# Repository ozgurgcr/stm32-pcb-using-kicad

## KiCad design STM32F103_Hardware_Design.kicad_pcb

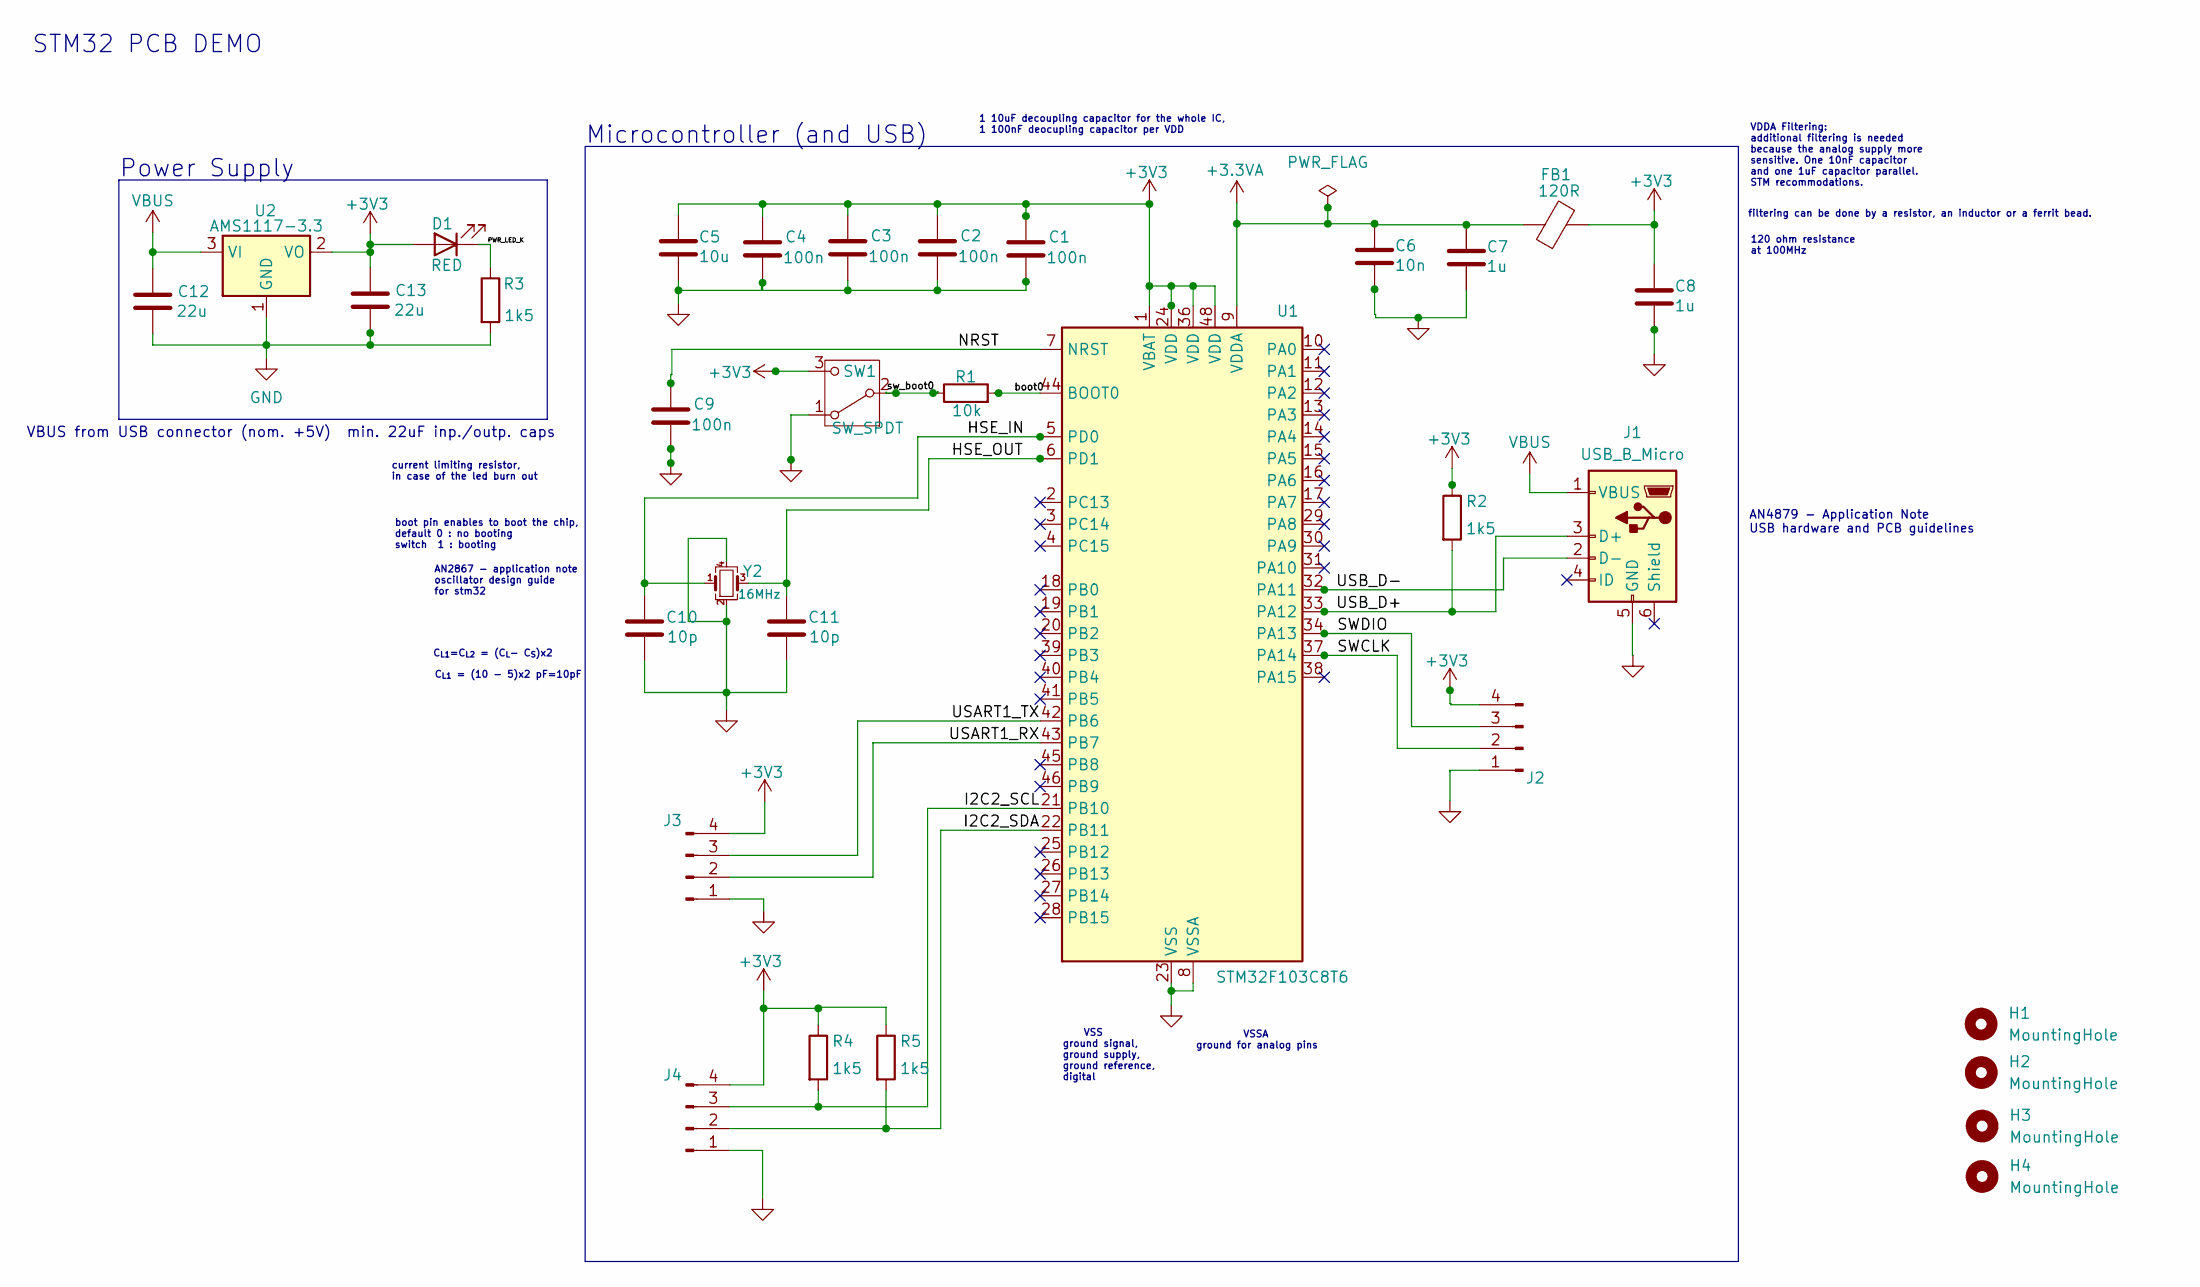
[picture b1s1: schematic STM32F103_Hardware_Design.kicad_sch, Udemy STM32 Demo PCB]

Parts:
C1, C2, C3, C4, C9: 100n; C_0402_1005Metric
C5: 10u; C_0603_1608Metric
C6: 10n; C_0402_1005Metric
C7, C8: 1u; C_0402_1005Metric
C10, C11: 10p; C_0402_1005Metric
C12, C13: 22u; C_0805_2012Metric
D1: RED; LED_0603_1608Metric
FB1: 120R; L_0603_1608Metric
H1, H2, H3, H4: MountingHole; MountingHole_2.2mm_M2
J1: USB_B_Micro; USB_Micro-B_Wuerth_629105150521
J2, J3, J4: Conn_01x04_Pin; PinHeader_1x04_P2.54mm_Vertical
R1: 10k; R_0402_1005Metric
R2, R3, R4, R5: 1k5; R_0402_1005Metric
SW1: SW_SPDT; SW_SPDT_PCM12
U1: STM32F103C8T6; LQFP-48_7x7mm_P0.5mm
U2: AMS1117-3.3; SOT-223-3_TabPin2
Y2: 16MHz; Crystal_SMD_3225-4Pin_3.2x2.5mm_HandSoldering

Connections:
+3.3VA: C6.1, C7.1, FB1.1, U1.9 (VDDA)
+3V3: C1.1, C2.1, C3.1, C4.1, C5.1, C8.1, C13.1, D1.2 (A), FB1.2, J2.4, J3.4, J4.4, R2.1, R4.1, R5.1, SW1.3 (C), U1.1 (VBAT), U1.24 (VDD), U1.36 (VDD), U1.48 (VDD), U2.2 (VO)
/HSE_IN: C10.1, U1.5 (PD0), Y2.1
/HSE_OUT: C11.1, U1.6 (PD1), Y2.3
/I2C2_SCL: J4.3, R4.2, U1.21 (PB10)
/I2C2_SDA: J4.2, R5.2, U1.22 (PB11)
/NRST: C9.1, U1.7 (NRST)
/PWR_LED_K: D1.1 (K), R3.1
/SWCLK: J2.2, U1.37 (PA14)
/SWDIO: J2.3, U1.34 (PA13)
/USART1_RX: J3.2, U1.43 (PB7)
/USART1_TX: J3.3, U1.42 (PB6)
/USB_D+: J1.3 (D+), R2.2, U1.33 (PA12)
/USB_D-: J1.2 (D-), U1.32 (PA11)
/boot0: R1.2, U1.44 (BOOT0)
/sw_boot0: R1.1, SW1.2 (B)
GND: C1.2, C2.2, C3.2, C4.2, C5.2, C6.2, C7.2, C8.2, C9.2, C10.2, C11.2, C12.2, C13.2, J1.5 (GND), J2.1, J3.1, J4.1, R3.2, SW1.1 (A), U1.8 (VSSA), U1.23 (VSS), U1.35 (VSS), U1.47 (VSS), U2.1 (GND), Y2.2, Y2.4
VBUS: C12.1, J1.1 (VBUS), U2.3 (VI)

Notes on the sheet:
AN4879 - Application Note USB hardware and PCB guidelines
120 ohm resistance at 100MHz
Power Supply
VDDA Filtering: additional filtering is needed because the analog supply more sensitive. One 10nF capacitor and one 1uF capacitor parallel. STM recommodations.
1 10uF decoupling capacitor for the whole IC, 1 100nF deocupling capacitor per VDD
VBUS from USB connector (nom. +5V) min. 22uF inp./outp. caps
C_{L1} = (10 - 5)x2 pF=10pF
filtering can be done by a resistor, an inductor or a ferrit bead.
VSSA ground for analog pins
Microcontroller (and USB)
C_{L1}=C_{L2} = (C_{L}- C_{S})x2
boot pin enables to boot the chip, default 0 : no booting switch 1 : booting
AN2867 - application note oscillator design guide for stm32
VSS ground signal, ground supply, ground reference, digital
current limiting resistor, in case of the led burn out
STM32 PCB DEMO

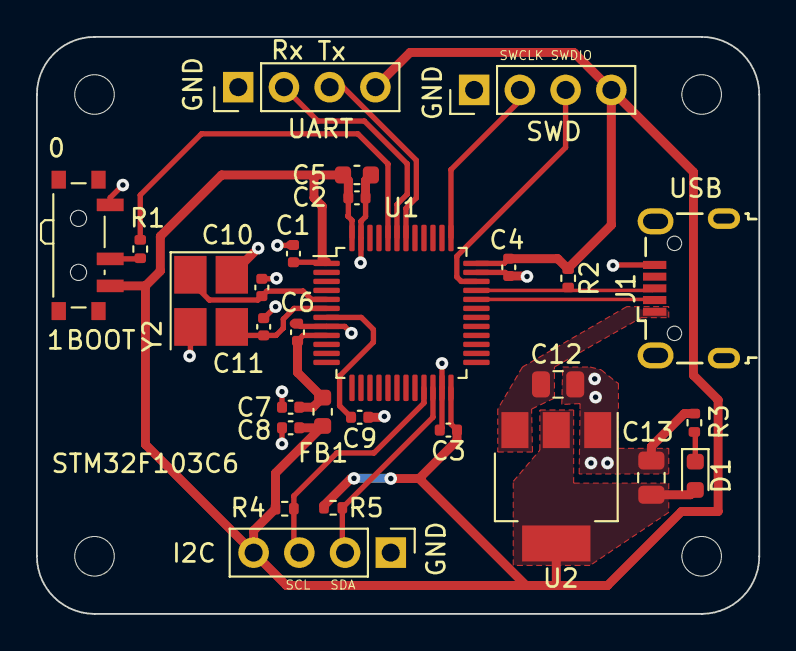
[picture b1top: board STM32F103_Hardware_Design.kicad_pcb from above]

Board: 2 copper layers, 40.1 x 32.1 mm, 32 parts (0 on the bottom side), 18 nets.

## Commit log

2024-06-11 stm32 pcb demo project schematic
2024-06-11 PCB layout and component alignment done,\n usb port 3d model added
2024-06-11 PCB done
2024-06-11 user logo added to PCB
